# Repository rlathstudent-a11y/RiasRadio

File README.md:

# Ria's Radio

Here's my submission for my radio!

### What does it do?
- For each key, a different note is played

### Challenges 
- It was my first time ever making a schematic or a 3d model, so it was very challenging to figure out how the applications function and how to use the numerous tools. But at the end of it, I became pretty good at using Shapr3D and in the future I hope to use it more to make models. 

### PCB

Here is a picture of my schematic and PCB: 

Schematic            |  PCB         |
:-------------------------:|:-------------------------:|
    |    | 

### CAD Model

This was made in Shapr3D. 

### Firmware

The firmware was made in VS Code using KMK. 

### BOM

- 1 XIAO RP2040
- 4 Blank DSA Keycaps
- 4 Cherry MX Switches

1 LS1 speaker (provided by me)

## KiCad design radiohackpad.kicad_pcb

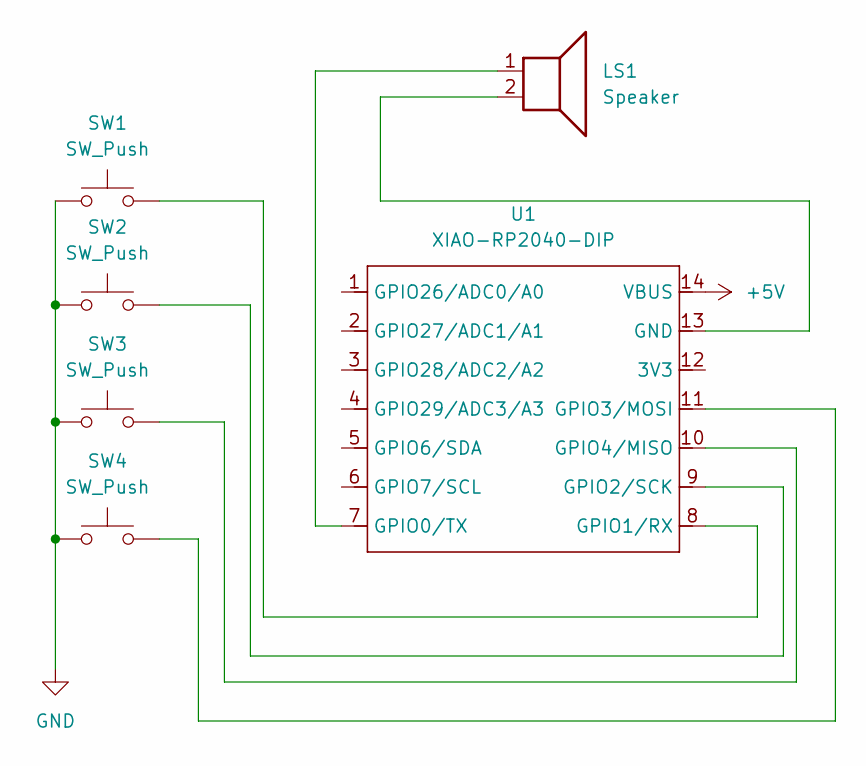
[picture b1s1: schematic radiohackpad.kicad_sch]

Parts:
LS1: Speaker; Speaker_CUI_CMR-1206S-67
SW1, SW2, SW3, SW4: SW_Push; SW_Cherry_MX_1.00u_PCB
U1: XIAO-RP2040-DIP

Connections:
+5V: U1.14 (VBUS)
GND: SW1.1, SW2.1, SW3.1, SW4.1
unnamed: LS1.2, U1.13 (GND)
unnamed: LS1.1, U1.7 (GPIO0/TX)
unnamed: SW1.2, U1.8 (GPIO1/RX)
unnamed: SW2.2, U1.9 (GPIO2/SCK)
unnamed: SW4.2, U1.11 (GPIO3/MOSI)
unnamed: SW3.2, U1.10 (GPIO4/MISO)

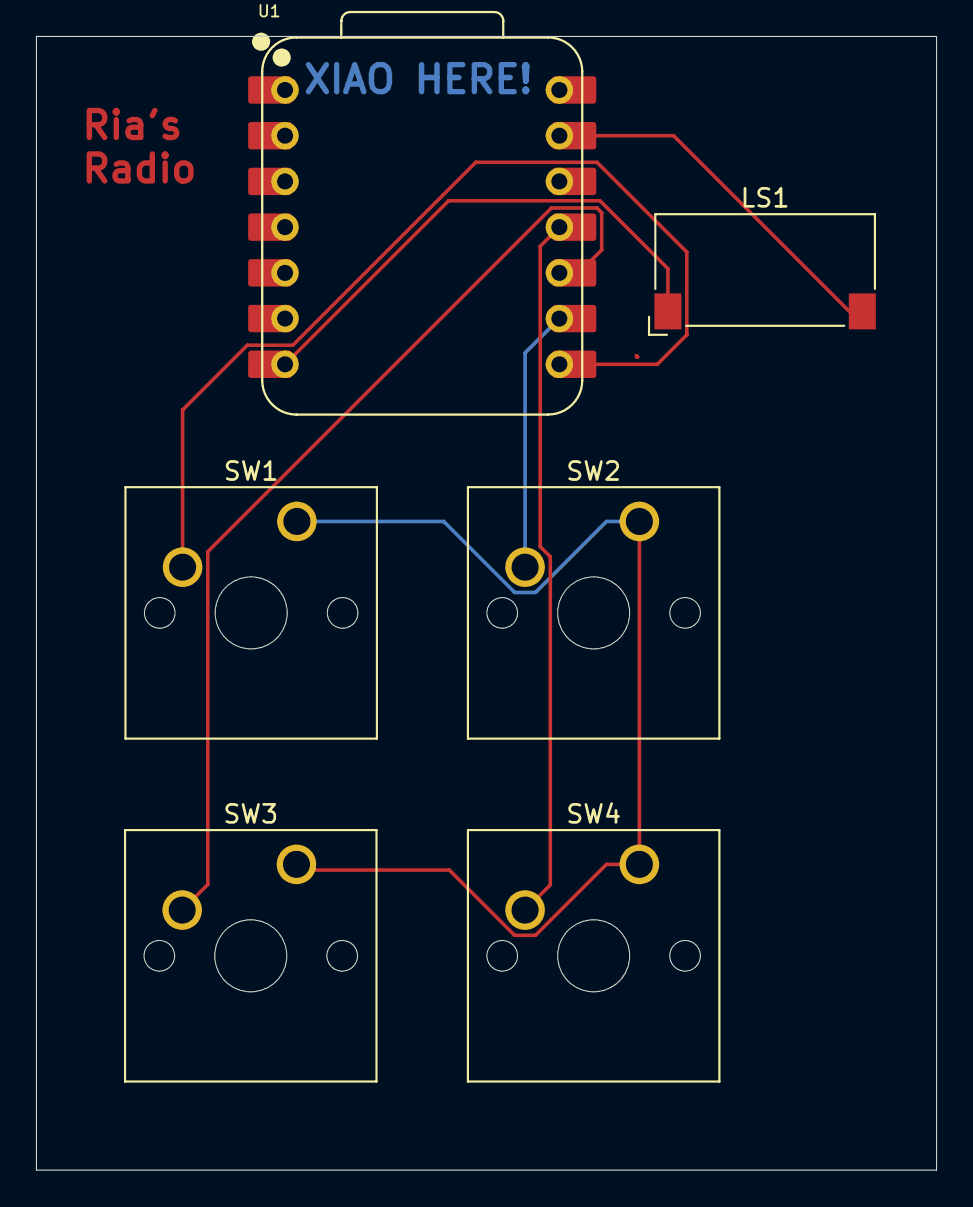
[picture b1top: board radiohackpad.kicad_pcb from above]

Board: 2 copper layers, 50.0 x 63.0 mm, 6 parts (0 on the bottom side), 7 nets.
